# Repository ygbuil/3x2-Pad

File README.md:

# 5-Key Keyboard Pad (Pro Micro-Based)

This project is a custom-built 5-key keyboard pad designed and developed entirely from scratch. It’s powered by a **Pro Micro microcontroller** and is fully compatible with **VIA Software**, a powerful configuration tool for custom keyboards.

## Features

- 5 fully customizable keys using VIA Software.
- Hotswap PCB, allowing for quick swap of Mechanical Switches.

## Project Journey

- **Custom PCB Design**  
  I designed the PCB from the ground up using **KiCad**, an open-source electronics design automation suite. The design files were sent to a professional manufacturer for production.

- **Manual Assembly**  
  Once the PCBs arrived, I soldered all components including diodes, Pro Micro and hotswap sockets.

- **Firmware Development**  
  I created and flashed the keyboard's firmware using **QMK Firmware**, an open source software widely used in the mechanical keyboard community. The keyboard is **VIA-compatible**. [VIA](https://usevia.app) is a user-friendly software that enables real-time keyboard customization through a simple graphical interface, allowing for key remaps, creation of macros, configuration of layers and more, without any coding involved.

## Process photos

Kicad modelling:

Soldering:

Final product:

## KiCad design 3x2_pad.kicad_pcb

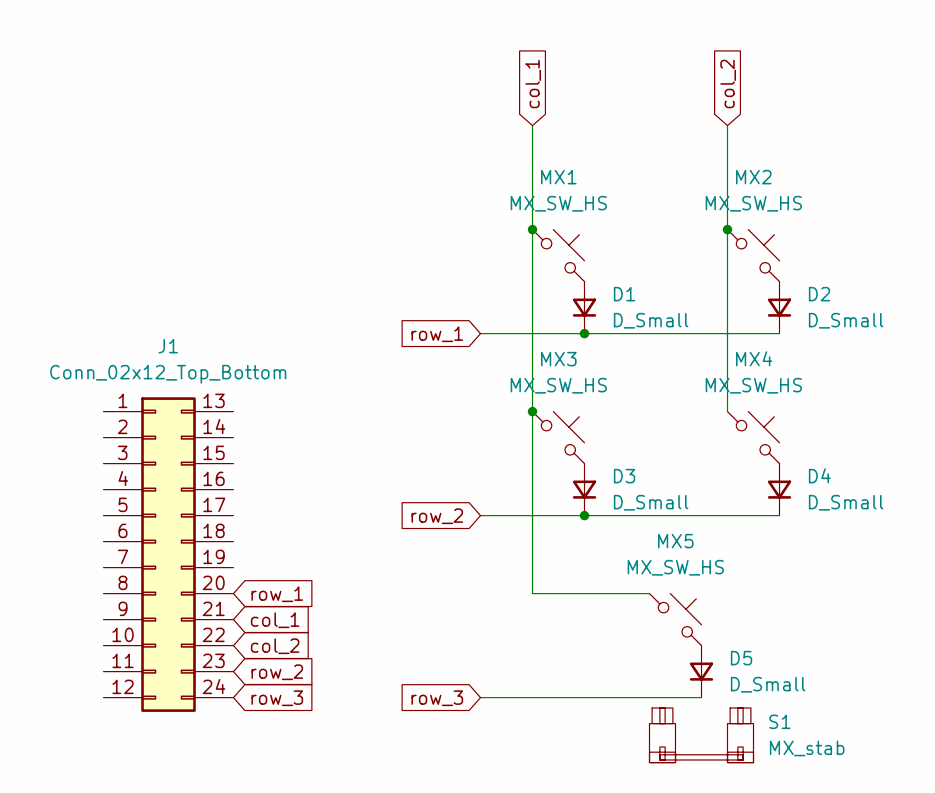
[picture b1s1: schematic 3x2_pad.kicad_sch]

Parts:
D1, D2, D3, D4, D5: D_Small; D_SOD-123
J1: Conn_02x12_Top_Bottom; ProMicro_USBup
MX1, MX2, MX3, MX4, MX5: MX_SW_HS; SW_MX_HS_CPG151101S11_1u
S1: MX_stab; STAB_MX_P_2u

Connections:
unnamed: D1.2 (A), MX1.2
unnamed: D2.2 (A), MX2.2
unnamed: D3.2 (A), MX3.2
unnamed: D4.2 (A), MX4.2
unnamed: D5.2 (A), MX5.2
col_1: J1.21, MX1.1, MX3.1, MX5.1
col_2: J1.22, MX2.1, MX4.1
row_1: D1.1 (K), D2.1 (K), J1.20
row_2: D3.1 (K), D4.1 (K), J1.23
row_3: D5.1 (K), J1.24

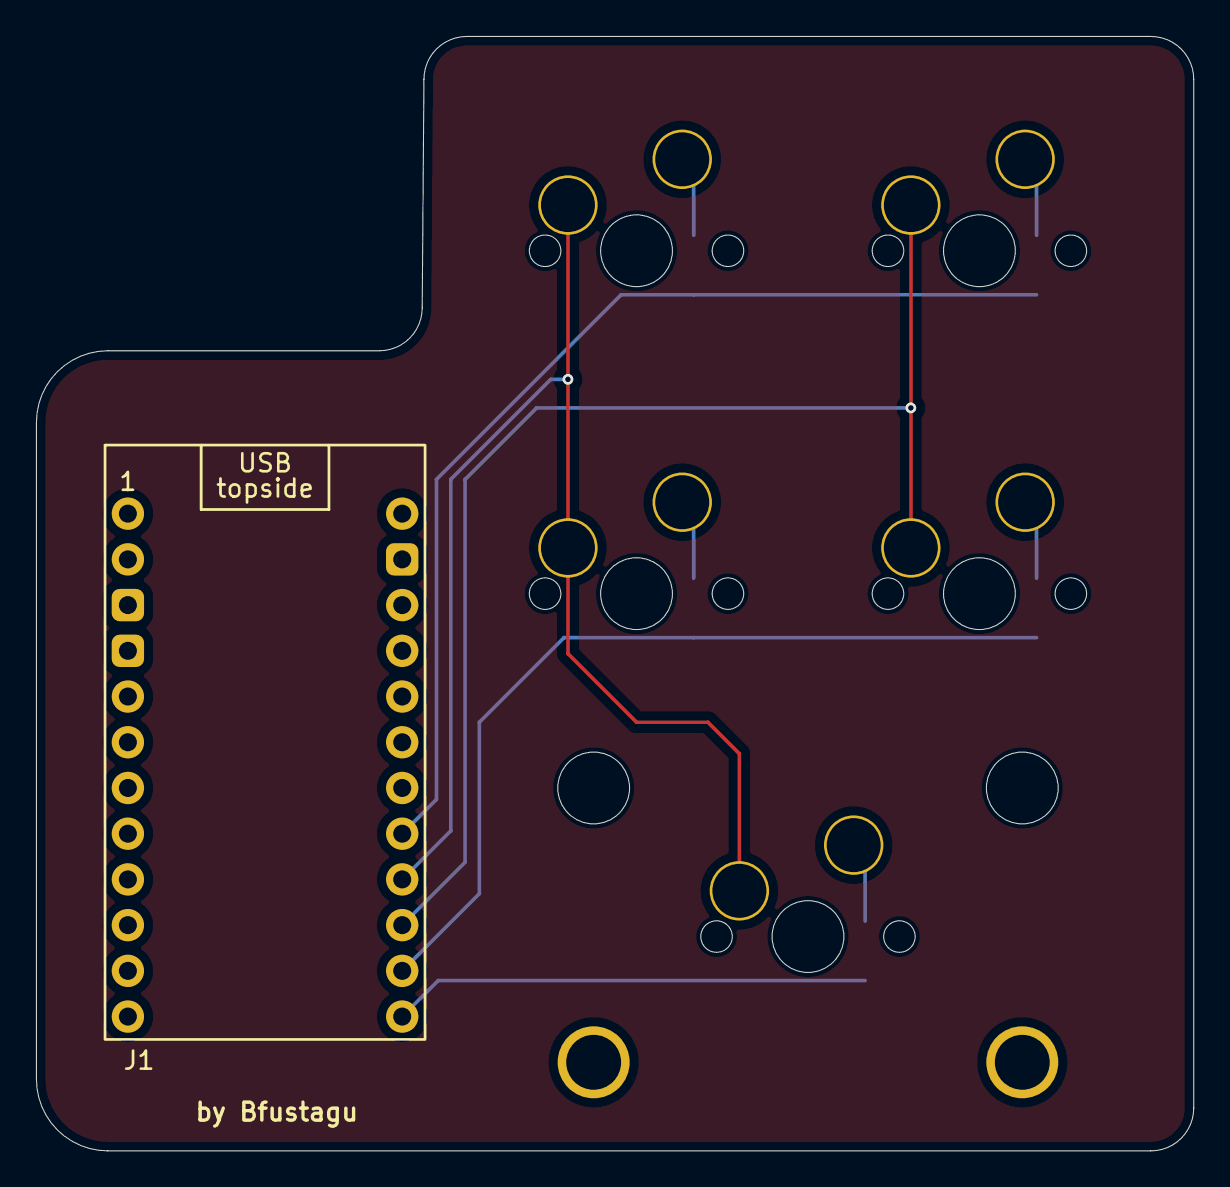
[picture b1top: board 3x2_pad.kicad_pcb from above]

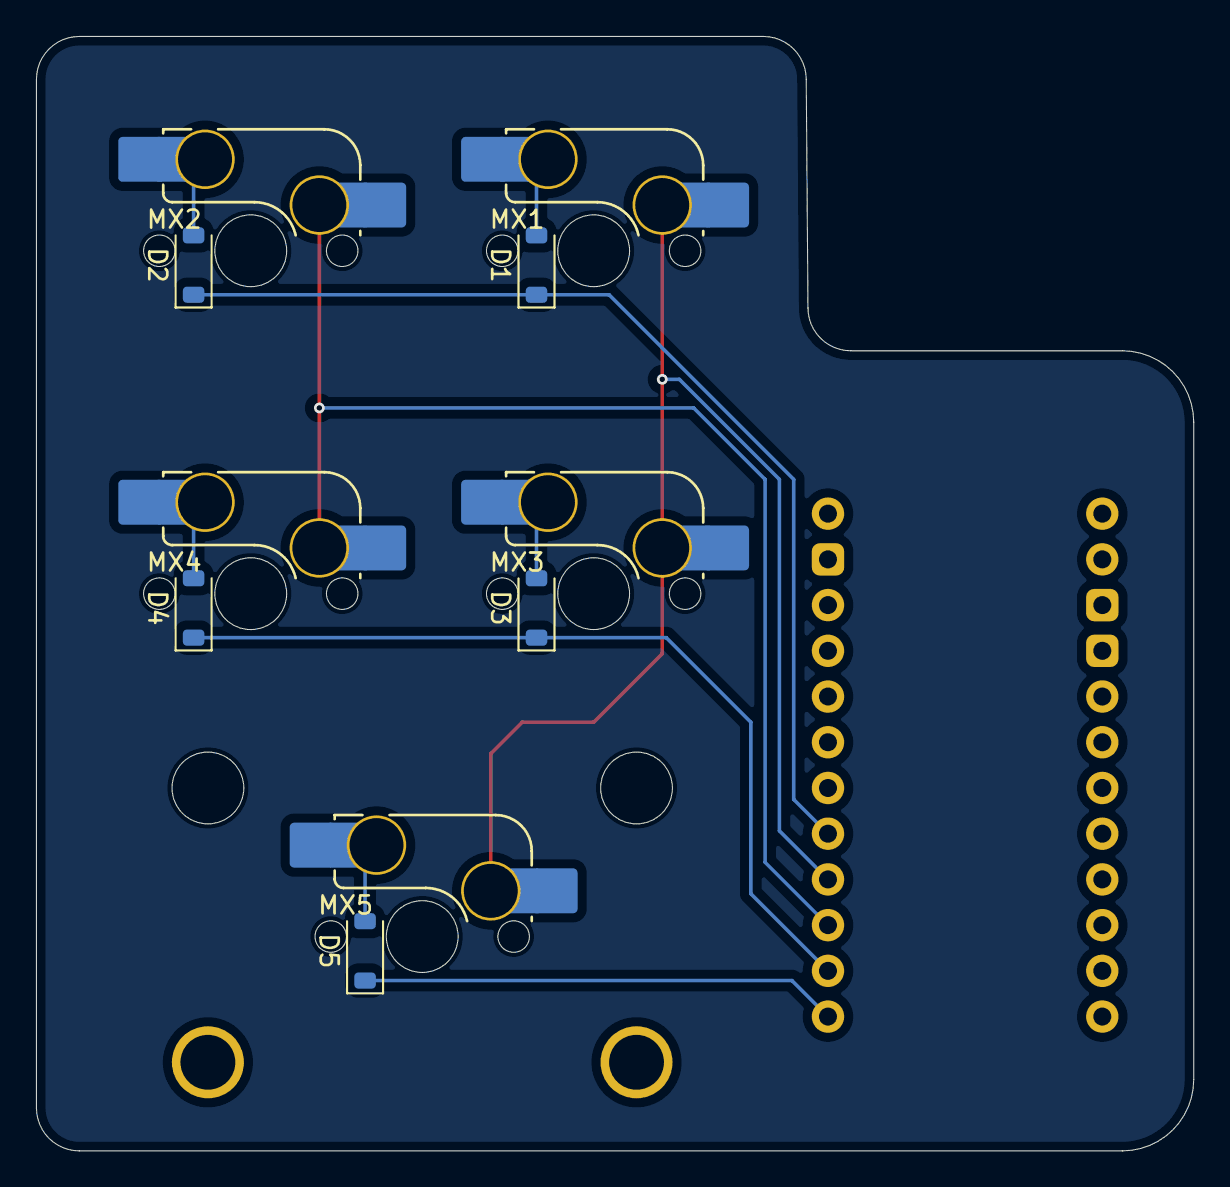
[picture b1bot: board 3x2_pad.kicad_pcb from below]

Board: 2 copper layers, 64.3 x 61.9 mm, 12 parts (10 on the bottom side), 10 nets.

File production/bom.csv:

Designator,Footprint,Quantity,Value,LCSC Part #
"D1, D2, D3, D4, D5",D_SOD-123,5,D_Small,
J1,ProMicro_USBup,1,Conn_02x12_Top_Bottom,
"MX1, MX2, MX3, MX4, MX5",SW_MX_HS_CPG151101S11_1u,5,MX_SW_HS,
S1,STAB_MX_P_2u,1,MX_stab,

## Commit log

2025-04-10 fisrt commit
2025-04-26 firmware
2025-04-26 pcb folder
2025-05-15 docs
